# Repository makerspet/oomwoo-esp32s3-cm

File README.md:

# oomwoo-esp32s3-cm

Spec TBD; Not decided if we need this or not.

Pi CM4/CM5-compatible Compute Module using ESP32-S3 instead of CPU

Purpose - cost reduced "educational" version of OOMWOO open-source vacuum cleaner
robot by replacing Pi CM4/CM5 with ESP32-S3, moving mapping/navigation compute to
a separate local PC running ROS2.

Tradeoffs:
- this is not a "consumer product" anymore due to the need to set up the additional ROS2 local PC
  - PC-to-ESP32-S3 Wi-Fi connection can suffer from dead reception zones, busy Wi-Fi
- no camera-based obstacle recognition

- mounts on [OOMWOO carrier I/O board](https://github.com/makerspet/oomwoo-io-board)
- pin-compatible CM4/CM5 Compute Module using ESP32-S3 (instead of CPU)
- expose GPIOs on CM4/CM5 headers
  - 1x serial to MCU
  - GPIOs (MCU acts as watchdog for ESP32-S3, can reset it if ESP32-S3 is unresponsive)
  - SPI (to IMU on I/O board)
  - I2C
  - 1x serial to LiDAR (via I/O board)
- Problem - no cameras, ESP32-S3 supports DVP parallel only, not MIPI

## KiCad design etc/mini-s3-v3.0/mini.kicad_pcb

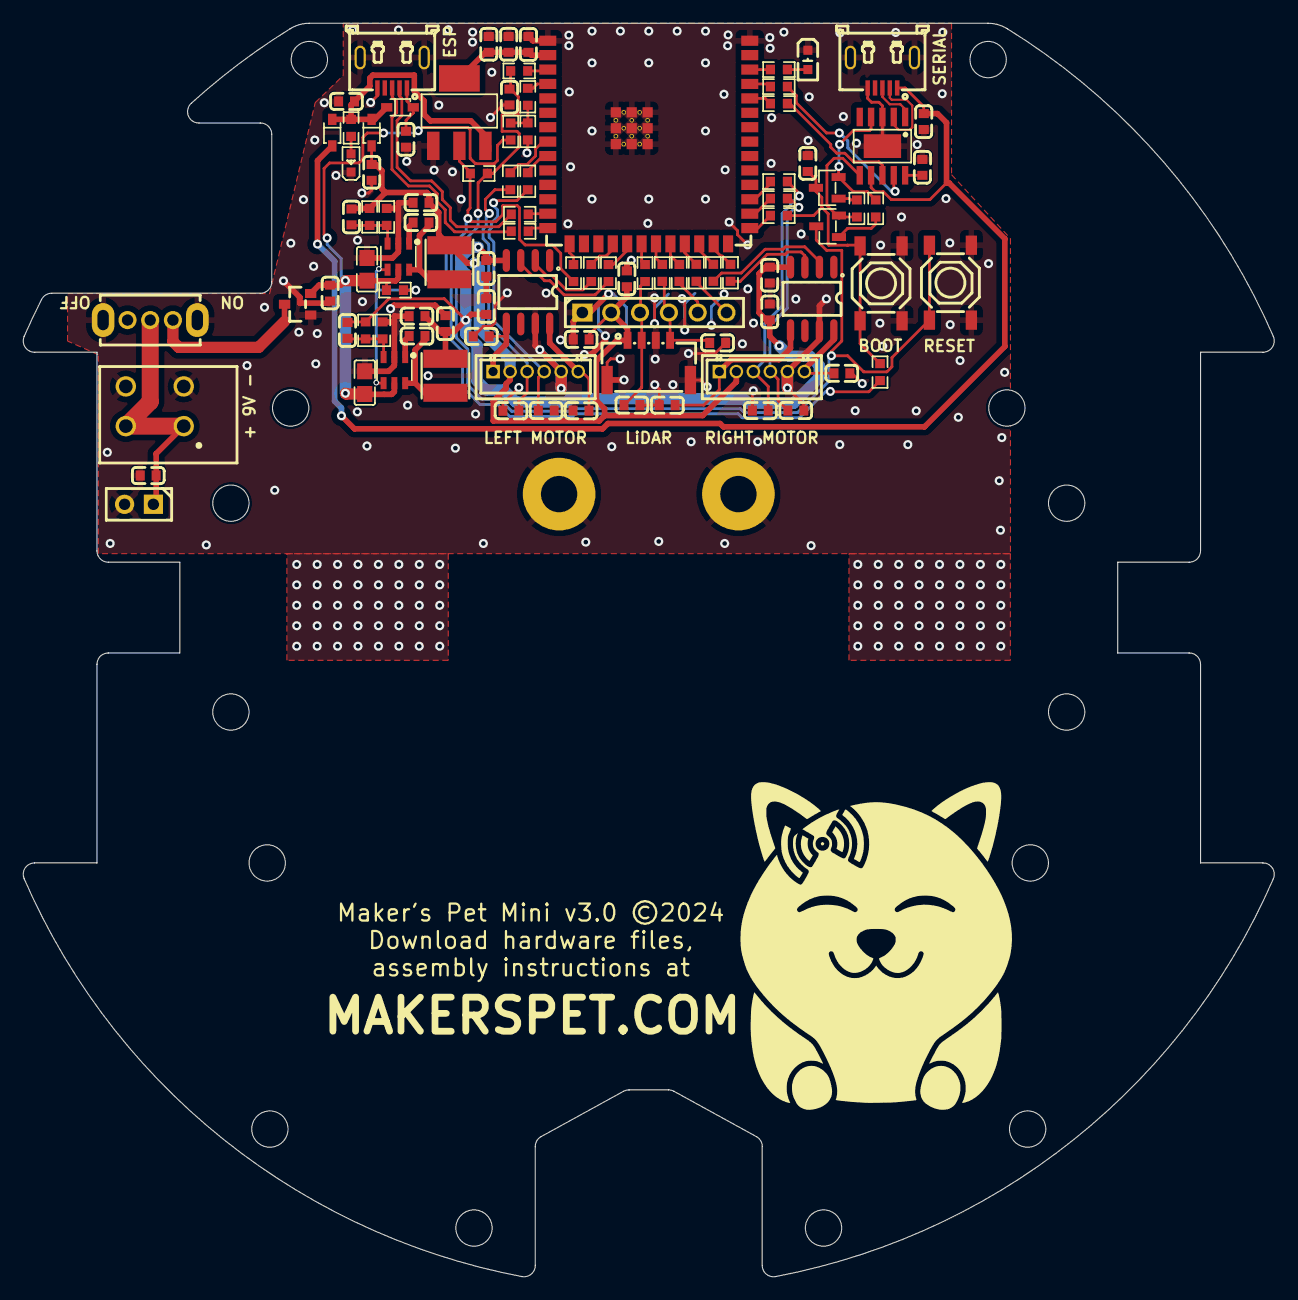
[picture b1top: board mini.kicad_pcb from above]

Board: 2 copper layers, 110.2 x 110.5 mm, 114 parts (0 on the bottom side), 71 nets.

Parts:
C1, C3, C18, C19, C21, C22, C23, C27: CC0603KRX7R9BB104; C0603
C2, C4, C7, C9, C13, C24, C25: CL10A226MP8NUNE; C0603
C5, C6, C10, C11: CL10B223KB8NNNC; C0603
C8, C12: CL21A226MAQNNNE; C0805
C14, C15, C16, C17, C20, C26, C28, C29, C30, C31, C32, C33, C34, C35, C36, C37: 0603B151K500NT; C0603
D1, D2, D3: 1N5819WS; SOD-323_L1.8-W1.3-LS2.5-RD
H1, H2, H3, H4, H5, H6, H7, H8, H9, H10, H11, H12, H13, H14: 3.2mm; MountingHole_3.2mm_M3
H15, H16: 3.2mm; MountingHole_3.2mm_M3_Pad
J1: 2685Y-106CNG1SNA01; HDR-TH_6P-P2.54-V-F
J2: MX250-3.5-02P-B-GY01-CU-A; CONN-TH_2P-MX250-3.5-02P-B-GY01-CU-A
J4, J7: ZH1.5-6A M; CONN-TH_6P-P1.50_ZH1.5-6A
J10: 22850102ANG1SYA02; HDR-TH_2P-P2.54-V-F
J13: 1.25-4PLTDK; CONN-SMD_4P-P1.25_SHOU_1.25-4PLTDK
L1, L2: FNR4030S100MT; IND-SMD_L4.0-W4.0_FNR40XXS
LED1: KT-0603R; LED0603-RD
LED2: KT-0603W; LED0603-R-RD_WHITE
Q1: AO3401A; SOT-23_L2.9-W1.3-P1.90-LS2.4-BR
Q2, Q3: SS8050_C2150; SOT-23-3_L2.9-W1.3-P1.90-LS2.4-BR
R1, R2, R10, R18, R19, R22, R23, R26, R27, R28, R30: 0603WAF5100T5E; R0603
R3: 0603WAF1000T5E; R0603
R4, R5, R7, R8, R9, R11, R12, R20, R21, R24, R25, R29, R40: 0603WAF1002T5E; R0603
R6: 0603WAF2702T5E; R0603
R13, R16, R17: 0603WAF1103T5E; R0603
R14: AECR0603F15K0K9; R0603
R15: 0603WAF9102T5E; R0603
R31, R32: 0603WAF0000T5E; R0603
SW1: SK12D07VG5; SW-TH_SK12D07VG5
SW2, SW3: TS-1187A-B-A-B; SW-SMD_4P-L5.1-W5.1-P3.70-LS6.5-TL-2
U1, U2: BDR6120H; SOP-8_L4.9-W3.8-P1.27-LS6.0-BL
U3: ESP32-S3-WROOM-1-N4; WIFIM-SMD_ESP32-S3-WROOM-1-N8
U4, U5: MT2492; SOT-23-6_L2.9-W1.6-P0.95-LS2.8-BL
U6: CH340K_C18208922; ESOP-10_L4.9-W3.9-P1.00-LS6.0-BL-EP
U7, U9: USB-MR-D-015; MICRO-USB-SMD_920-C52A2021S10105
U8: AMS1117-3.3; SOT-223-3_L6.5-W3.4-P2.30-LS7.0-BR

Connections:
+3V3: C14.1, C23.2, C24.2, U3.2 (3V3), U8.4 (VOUT)
+3V3B: R17.2, R29.2, R40.2, U8.2 (VOUT)
+5V: C5.2, C7.2, C9.2, C15.1, C37.1, D1.2 (A), J1.2, J4.2, J7.2, J13.1, L1.2, R13.2
+5VL: C25.2, D1.1 (K), D2.1 (K), D3.1 (K), R10.2, U8.3 (VIN)
+6V: C1.2, C2.2, C3.2, C4.2, C6.2, C13.2, C16.1, L2.2, R15.2, U1.4 (VDD), U2.4 (VDD)
+BATT: C8.2, C12.2, C17.1, Q1.2 (S), R6.2, R16.1, U4.5 (IN), U5.5 (IN)
/ADC_BAT: R27.2, U3.4 (IO4)
/A_BAT: R6.1, R8.2, R27.1
/DTR: Q3.2 (E), R24.1, U6.4 (~DTR)
/E: C19.2, Q2.3 (C), R17.1, R28.1, SW3.1 (A), SW3.2 (B)
/EA_LEFT: C29.1, J4.4, R20.2
/EA_RIGHT: C30.1, J7.4, R5.2
/EB_LEFT: C31.1, J4.3, R21.2
/EB_RIGHT: C32.1, J7.3, R4.2
/EN: R28.2, U3.3 (EN)
/ENC_A_LEFT: R20.1, U3.9 (IO16)
/ENC_A_RIGHT: R5.1, U3.28 (IO35)
/ENC_B_LEFT: R21.1, U3.8 (IO15)
/ENC_B_RIGHT: R4.1, U3.29 (IO36)
/GP0: C18.2, Q3.3 (C), R29.1, R30.2, SW2.1 (A), SW2.2 (B)
/GP2: LED2.1 (A), R3.2
/GPIO0: R30.1, U3.27 (IO0)
/GPIO2: R3.1, U3.38 (IO2)
/IN1_L: R1.1, U1.2 (INA)
/IN1_LEFT: R1.2, U3.18 (IO10)
/IN1_R: R22.1, U2.2 (INA)
/IN1_RIGHT: R22.2, U3.24 (IO47)
/IN2_L: R2.1, U1.3 (INB)
/IN2_LEFT: R2.2, U3.19 (IO11)
/IN2_R: R19.1, U2.3 (INB)
/IN2_RIGHT: R19.2, U3.25 (IO48)
/JTAG_STRAP: R40.1, U3.15 (IO3)
/LIDAR_EN: R12.2, U3.23 (IO21)
/LIDAR_PWM: R9.2, U3.22 (IO14)
/LIDAR_RX: R23.2, U3.21 (IO13)
/LIDAR_TX: R11.2, U3.20 (IO12)
/L_EN: J1.6, R12.1
/L_PWM: J1.5, R9.1
/L_RX: C36.1, J1.4, J13.4, R23.1
/L_TX: C35.1, J1.3, J13.2, R11.1
/M+LEFT: C33.1, J4.6, U1.8 (OUTA)
/M+RIGHT: C34.1, J7.6, U2.8 (OUTA)
/M-LEFT: C20.1, J4.1, U1.5 (OUTB)
/M-RIGHT: C28.1, J7.1, U2.5 (OUTB)
/RTS: Q2.2 (E), R25.1, U6.6 (~RTS)
/RXD: R26.2, U6.8 (TXD)
/RXD0: R26.1, U3.36 (RXD0)
/TXD: R18.2, U6.9 (RXD)
/TXD0: R18.1, U3.37 (TXD0)
/USB_DN: U6.2 (UD-), U7.2 (D-)
/USB_DN_E: R32.1, U9.2 (D-)
/USB_DN_ESP: R32.2, U3.13 (IO19)
/USB_DP: U6.1 (UD+), U7.3 (D+)
/USB_DP_E: R31.1, U9.3 (D+)
/USB_DP_ESP: R31.2, U3.14 (IO20)
GND: C1.1, C2.1, C3.1, C4.1, C7.1, C8.1, C9.1, C12.1, C13.1, C14.2, C15.2, C16.2, C17.2, C18.1, C19.1, C20.2, C21.1, C22.1, C23.1, C24.1, C25.1, C26.2, C27.1, C28.2, C29.2, C30.2, C31.2, C32.2, C33.2, C34.2, C35.2, C36.2, C37.2, H15.1, H16.1, J1.1, J2.2, J2.2B, J4.5, J7.5, J10.2, J13.3, J13.5, J13.6, LED1.1 (K), LED2.2 (K), Q1.1 (G), R7.1, R8.1, R14.1, SW1.4, SW1.5, SW2.3 (C), SW2.4 (D), SW3.3 (C), SW3.4 (D), U1.7 (GND), U2.7 (GND), U3.1 (GND), U3.40 (GND), U3.41 (GND), U4.2 (GND), U5.2 (GND), U6.3 (GND), U6.11 (GND), U7.5 (GND), U7.6 (EH), U7.7 (EH), U8.1 (GND), U9.5 (GND), U9.6 (EH), U9.7 (EH)
unnamed: C26.1, J2.1, J2.1B, J10.1, SW1.2
unnamed: LED1.2 (A), R10.1
unnamed: Q1.3 (D), SW1.1
unnamed: Q2.1 (B), R24.2
unnamed: Q3.1 (B), R25.2
unnamed: C10.1, U4.1 (BS)
unnamed: R16.2, U4.4 (EN), U5.4 (EN)
unnamed: C5.1, R13.1, R14.2, U4.3 (FB)
unnamed: C10.2, L1.1, U4.6 (SW)
unnamed: C11.1, U5.1 (BS)
unnamed: C6.1, R7.2, R15.1, U5.3 (FB)
unnamed: C11.2, L2.1, U5.6 (SW)
unnamed: C21.2, U6.10 (V3)
VUSB: C22.2, D3.2 (A), U6.7 (VCC), U7.1 (VBUS)
VUSB_ESP: C27.2, D2.2 (A), U9.1 (VBUS)

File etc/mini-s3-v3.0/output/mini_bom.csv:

"Comment","Designator","Footprint","LCSC Part Number"
"0603B151K500NT","C14,C15,C16,C17,C26,C37","C0603","C1594"
"SS8050_C2150","Q2,Q3","SOT-23-3_L2.9-W1.3-P1.90-LS2.4-BR","C2150"
"KT-0603R","LED1","LED0603-RD","C2286"
"KT-0603W","LED2","LED0603-R-RD_WHITE","C2290"
"AMS1117-3.3","U8","SOT-223-3_L6.5-W3.4-P2.30-LS7.0-BR","C6186"
"CC0603KRX7R9BB104","C1,C3,C18,C19,C21,C22,C23,C27","C0603","C14663"
"AO3401A","Q1","SOT-23_L2.9-W1.3-P1.90-LS2.4-BR","C15127"
"CL10B223KB8NNNC","C10,C11","C0603","C21122"
"0603WAF0000T5E","R31,R32","R0603","C21189"
"0603WAF1000T5E","R3","R0603","C22775"
"0603WAF2702T5E","R6","R0603","C22967"
"0603WAF5100T5E","R1,R2,R10,R18,R19,R22,R23,R26,R27,R28,R30","R0603","C23193"
"0603WAF9102T5E","R15","R0603","C23265"
"0603WAF1002T5E","R4,R5,R7,R8,R9,R11,R12,R20,R21,R24,R25,R29,R40","R0603","C25804"
"0603WAF1103T5E","R13,R16,R17","R0603","C25805"
"CL21A226MAQNNNE","C8,C12","C0805","C45783"
"CL10A226MP8NUNE","C2,C4,C7,C9,C13,C24,C25","C0603","C86295"
"MT2492","U4,U5","SOT-23-6_L2.9-W1.6-P0.95-LS2.8-BL","C89358"
"ZH1.5-6A M","J4,J7","CONN-TH_6P-P1.50_ZH1.5-6A","C146013"
"FNR4030S100MT","L1,L2","IND-SMD_L4.0-W4.0_FNR40XXS","C167879"
"1N5819WS","D1,D2,D3","SOD-323_L1.8-W1.3-LS2.5-RD","C191023"
"TS-1187A-B-A-B","SW2,SW3","SW-SMD_4P-L5.1-W5.1-P3.70-LS6.5-TL-2","C318884"
"AECR0603F15K0K9","R14","R0603","C328339"
"SK12D07VG5","SW1","SW-TH_SK12D07VG5","C431548"
"ESP32-S3-WROOM-1-N4","U3","WIFIM-SMD_ESP32-S3-WROOM-1-N8","C2913197"
"USB-MR-D-015","U7,U9","MICRO-USB-SMD_920-C52A2021S10105","C2926986"
"BDR6120H","U1,U2","SOP-8_L4.9-W3.8-P1.27-LS6.0-BL","C3007876"
"1.25-4PLTDK","J13","CONN-SMD_4P-P1.25_SHOU_1.25-4PLTDK","C3008549"
"MX250-3.5-02P-B-GY01-CU-A","J2","CONN-TH_2P-MX250-3.5-02P-B-GY01-CU-A","C7470116"
"CH340K_C18208922","U6","ESOP-10_L4.9-W3.9-P1.00-LS6.0-BL-EP","C18208922"

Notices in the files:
etc/mini-s3-v3.0/mini.kicad_pcb:
Maker's Pet Mini v3.0 ©2024
